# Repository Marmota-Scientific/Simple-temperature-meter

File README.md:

# Simple temperature meter

A simple 15-bit digital temperature meter capable of reading temperatures ranging from –200C to 500C (dependent on reference resistor and used probe). The meter is designed to work with platinum resistance temperature detectors PT100 and PT1000, which are converted into digital values with the usage of a MAX31865 ADC with a nominal temperature resolution of 0.03125C over full range.  

### Connectivity  

- USB 1.1 USB C  

- Handles programming and data output

### User interface

- 2 x 16 character LCD display
- 2 LEDs for user adjustable temperature level alarms  
- Rotary encoder with button  

### Power supply

- Designed to work on a 9V battery
- Operational input voltage level 18V – 5V  
- TPS7A26 linear voltage regulator

### ADC

- MAX31865 15-Bit ADC

### MCU

- RP2040 MCU
- 12 MHz clock speed

## Revision history

- The first working prototype
- Focus on compact sizing over all

### Revision 2.X

- Focus shifted to ease of construction
- Board dimensions and mounting holes match screen spesification

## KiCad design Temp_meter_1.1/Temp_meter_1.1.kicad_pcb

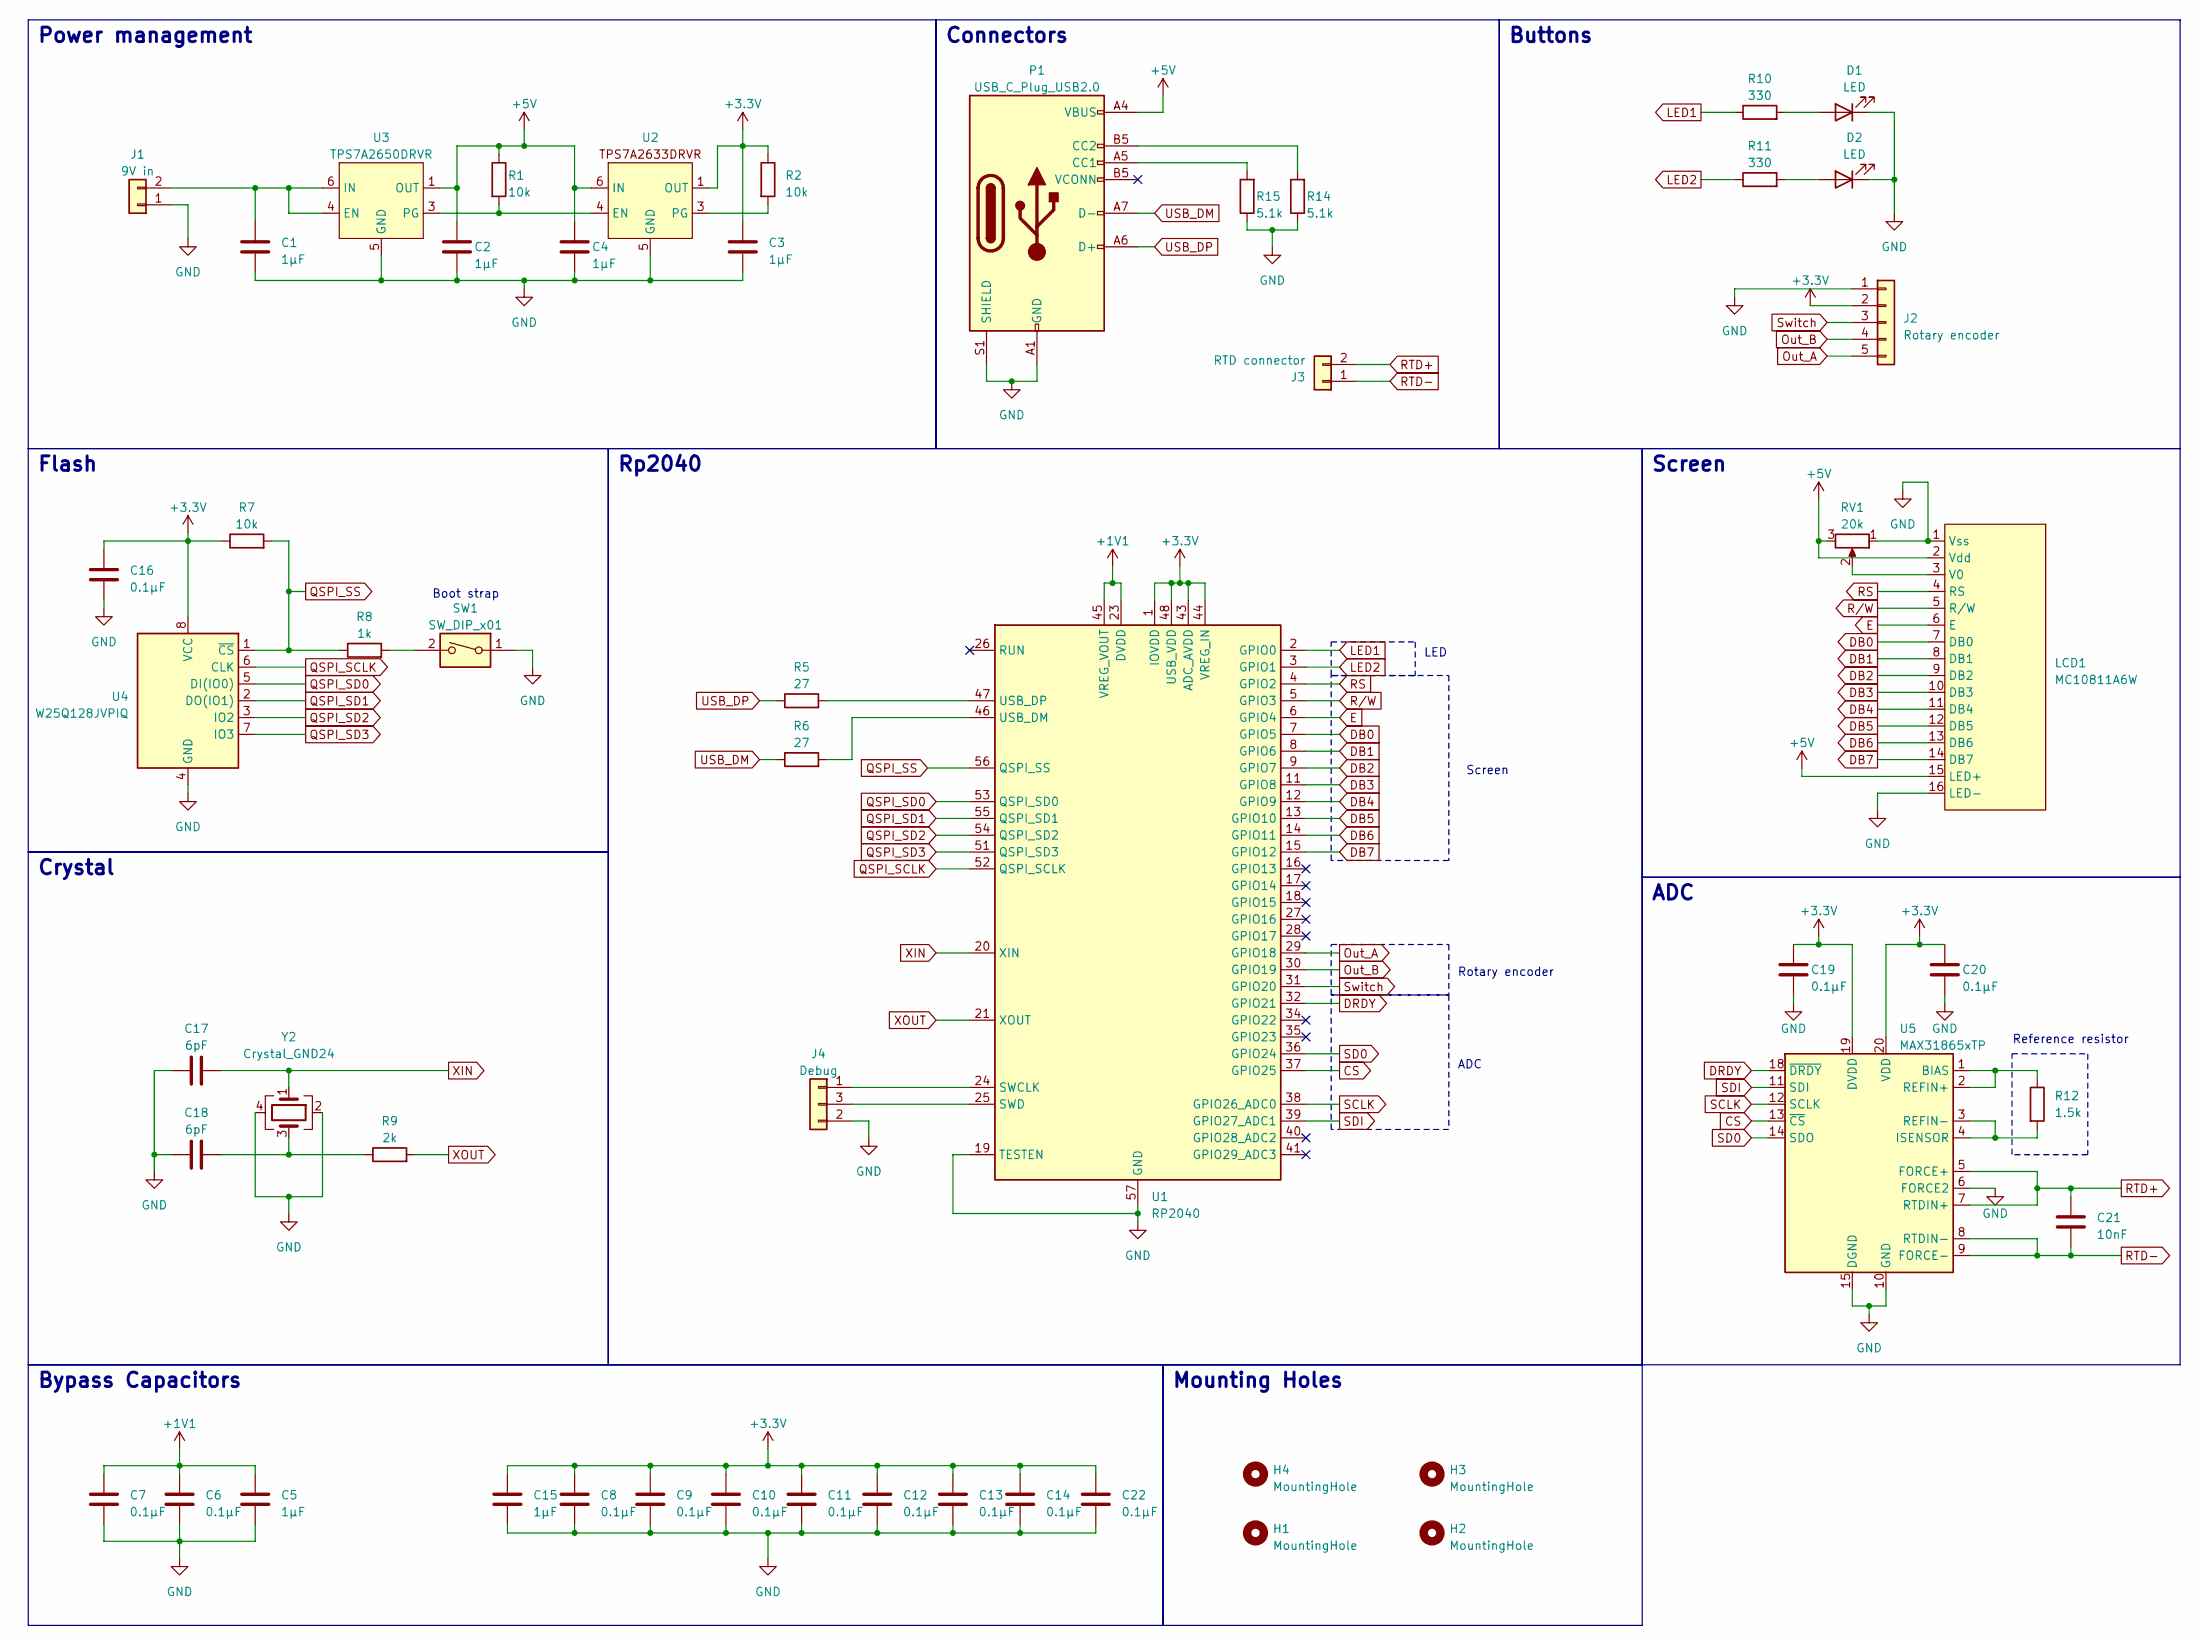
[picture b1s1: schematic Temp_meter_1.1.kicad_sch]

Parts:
C1, C2, C3, C4: 1µF; C_0603_1608Metric
C5, C15: 1µF; C_0201_0603Metric
C6, C7, C8, C9, C10, C11, C12, C13, C14, C16, C19, C20, C22: 0.1µF; C_0201_0603Metric
C17, C18: 6pF; C_0201_0603Metric
C21: 10nF; C_0402_1005Metric
D1, D2: LED; PinHeader_1x02_P1.00mm_Vertical
H1, H2, H3, H4: MountingHole; MountingHole_2.2mm_M2_DIN965_Pad
J1: 9V in; SolderWire-0.1sqmm_1x02_P3.6mm_D0.4mm_OD1mm
J2: Rotary encoder; PinHeader_1x05_P1.00mm_Vertical
J3: RTD connector; SolderWire-0.1sqmm_1x02_P3.6mm_D0.4mm_OD1mm
J4: Debug; PinHeader_1x03_P1.00mm_Vertical
LCD1: MC10811A6W; PinHeader_1x16_P1.00mm_Vertical
P1: USB_C_Plug_USB2.0; USB_C_Receptacle_Amphenol_12401610E4-2A_CircularHoles
R1, R2, R7: 10k; R_0402_1005Metric
R5, R6: 27; R_0603_1608Metric
R8: 1k; R_0402_1005Metric
R9: 2k; R_0402_1005Metric
R10, R11: 330; R_0603_1608Metric
R12: 1.5k; R_0805_2012Metric
R14, R15: 5.1k; R_0603_1608Metric
RV1: 20k; Potentiometer_Bourns_TC33X_Vertical
SW1: SW_DIP_x01; PinHeader_1x02_P1.00mm_Vertical
U1: RP2040; QFN-56-1EP_7x7mm_P0.4mm_EP3.2x3.2mm
U2: TPS7A2633DRVR; SON65P200X200X80-7N
U3: TPS7A2650DRVR; SON65P200X200X80-7N
U4: W25Q128JVPIQ; SON127P610X510X80-8N430X340
U5: MAX31865xTP; TQFN-20-1EP_5x5mm_P0.65mm_EP3.25x3.25mm
Y2: Crystal_GND24; Crystal_SMD_3225-4Pin_3.2x2.5mm

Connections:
+1V1: C5.1, C6.1, C7.1, U1.23 (DVDD), U1.45 (VREG_VOUT), U1.50 (DVDD)
+3.3V: C3.1, C8.1, C9.1, C10.1, C11.1, C12.1, C13.1, C14.1, C15.1, C16.1, C19.1, C20.1, C22.1, J2.2, R2.1, R7.1, U1.1 (IOVDD), U1.10 (IOVDD), U1.22 (IOVDD), U1.33 (IOVDD), U1.42 (IOVDD), U1.43 (ADC_AVDD), U1.44 (VREG_IN), U1.48 (USB_VDD), U1.49 (IOVDD), U2.1 (OUT), U4.8 (VCC), U5.19 (DVDD), U5.20 (VDD)
+5V: C2.1, C4.1, LCD1.2 (Vdd), LCD1.15 (LED+), P1.A4 (VBUS), P1.A9 (VBUS), P1.B4 (VBUS), P1.B9 (VBUS), R1.1, RV1.3, U2.6 (IN), U3.1 (OUT)
CS: U1.37 (GPIO25), U5.13 (~CS)
DB0: LCD1.7 (DB0), U1.7 (GPIO5)
DB1: LCD1.8 (DB1), U1.8 (GPIO6)
DB2: LCD1.9 (DB2), U1.9 (GPIO7)
DB3: LCD1.10 (DB3), U1.11 (GPIO8)
DB4: LCD1.11 (DB4), U1.12 (GPIO9)
DB5: LCD1.12 (DB5), U1.13 (GPIO10)
DB6: LCD1.13 (DB6), U1.14 (GPIO11)
DB7: LCD1.14 (DB7), U1.15 (GPIO12)
DRDY: U1.32 (GPIO21), U5.18 (~DRDY)
E: LCD1.6 (E), U1.6 (GPIO4)
GND: C1.2, C2.2, C3.2, C4.2, C5.2, C6.2, C7.2, C8.2, C9.2, C10.2, C11.2, C12.2, C13.2, C14.2, C15.2, C16.2, C17.1, C18.1, C19.2, C20.2, C22.2, D1.1 (K), D2.1 (K), J1.1, J2.1, J4.2, LCD1.1 (Vss), LCD1.16 (LED-), P1.A1 (GND), P1.A12 (GND), P1.B1 (GND), P1.B12 (GND), P1.S1 (SHIELD), R14.1, R15.1, RV1.1, SW1.1, U1.19 (TESTEN), U1.57 (GND), U2.5 (GND), U3.5 (GND), U4.4 (GND), U5.6 (FORCE2), U5.10 (GND), U5.15 (DGND), U5.16 (GND), U5.21 (GND), Y2.2, Y2.4
LED1: R10.1, U1.2 (GPIO0)
LED2: R11.1, U1.3 (GPIO1)
unnamed: C18.2, R9.1, Y2.3
unnamed: D1.2 (A), R10.2
unnamed: D2.2 (A), R11.2
unnamed: C1.1, J1.2, U3.4 (EN), U3.6 (IN)
unnamed: J4.1, U1.24 (SWCLK)
unnamed: J4.3, U1.25 (SWD)
unnamed: LCD1.3 (V0), RV1.2
unnamed: P1.A5 (CC1), R15.2
unnamed: P1.B5 (CC2), R14.2
unnamed: R8.2, SW1.2
unnamed: R6.2, U1.46 (USB_DM)
unnamed: R5.2, U1.47 (USB_DP)
unnamed: R1.2, U2.4 (EN), U3.3 (PG)
unnamed: R2.2, U2.3 (PG)
unnamed: R12.1, U5.1 (BIAS), U5.2 (REFIN+)
unnamed: R12.2, U5.3 (REFIN-), U5.4 (ISENSOR)
Out_A: J2.5, U1.29 (GPIO18)
Out_B: J2.4, U1.30 (GPIO19)
QSPI_SCLK: U1.52 (QSPI_SCLK), U4.6 (CLK)
QSPI_SD0: U1.53 (QSPI_SD0), U4.5 (DI(IO0))
QSPI_SD1: U1.55 (QSPI_SD1), U4.2 (DO(IO1))
QSPI_SD2: U1.54 (QSPI_SD2), U4.3 (IO2)
QSPI_SD3: U1.51 (QSPI_SD3), U4.7 (IO3)
QSPI_SS: R7.2, R8.1, U1.56 (QSPI_SS), U4.1 (~CS)
RS: LCD1.4 (RS), U1.4 (GPIO2)
RTD+: C21.1, J3.2, U5.5 (FORCE+), U5.7 (RTDIN+)
RTD-: C21.2, J3.1, U5.8 (RTDIN-), U5.9 (FORCE-)
R/W: LCD1.5 (R/W), U1.5 (GPIO3)
SCLK: U1.38 (GPIO26_ADC0), U5.12 (SCLK)
SD0: U1.36 (GPIO24), U5.14 (SDO)
SDI: U1.39 (GPIO27_ADC1), U5.11 (SDI)
Switch: J2.3, U1.31 (GPIO20)
USB_DM: P1.A7 (D-), R6.1
USB_DP: P1.A6 (D+), R5.1
XIN: C17.2, U1.20 (XIN), Y2.1
XOUT: R9.2, U1.21 (XOUT)

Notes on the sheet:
Rotary encoder
Buttons
Screen
Reference resistor
Bypass Capacitors
Mounting Holes
Flash
Connectors
Rp2040
Boot strap
Power management
LED
ADC
Crystal

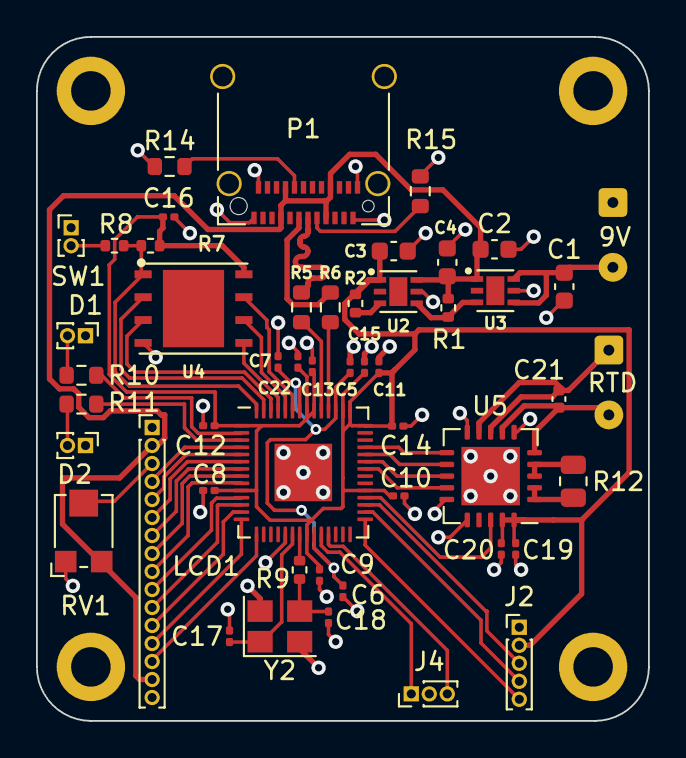
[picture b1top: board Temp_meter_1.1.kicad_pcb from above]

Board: 2 copper layers, 34.0 x 38.0 mm, 54 parts (0 on the bottom side), 53 nets.

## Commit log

2024-01-28 Create Pictures
2024-01-28 Rename 20231130_173424.jpg to Assembly.jpg
2024-01-29 Add files via upload
    Initial commit
